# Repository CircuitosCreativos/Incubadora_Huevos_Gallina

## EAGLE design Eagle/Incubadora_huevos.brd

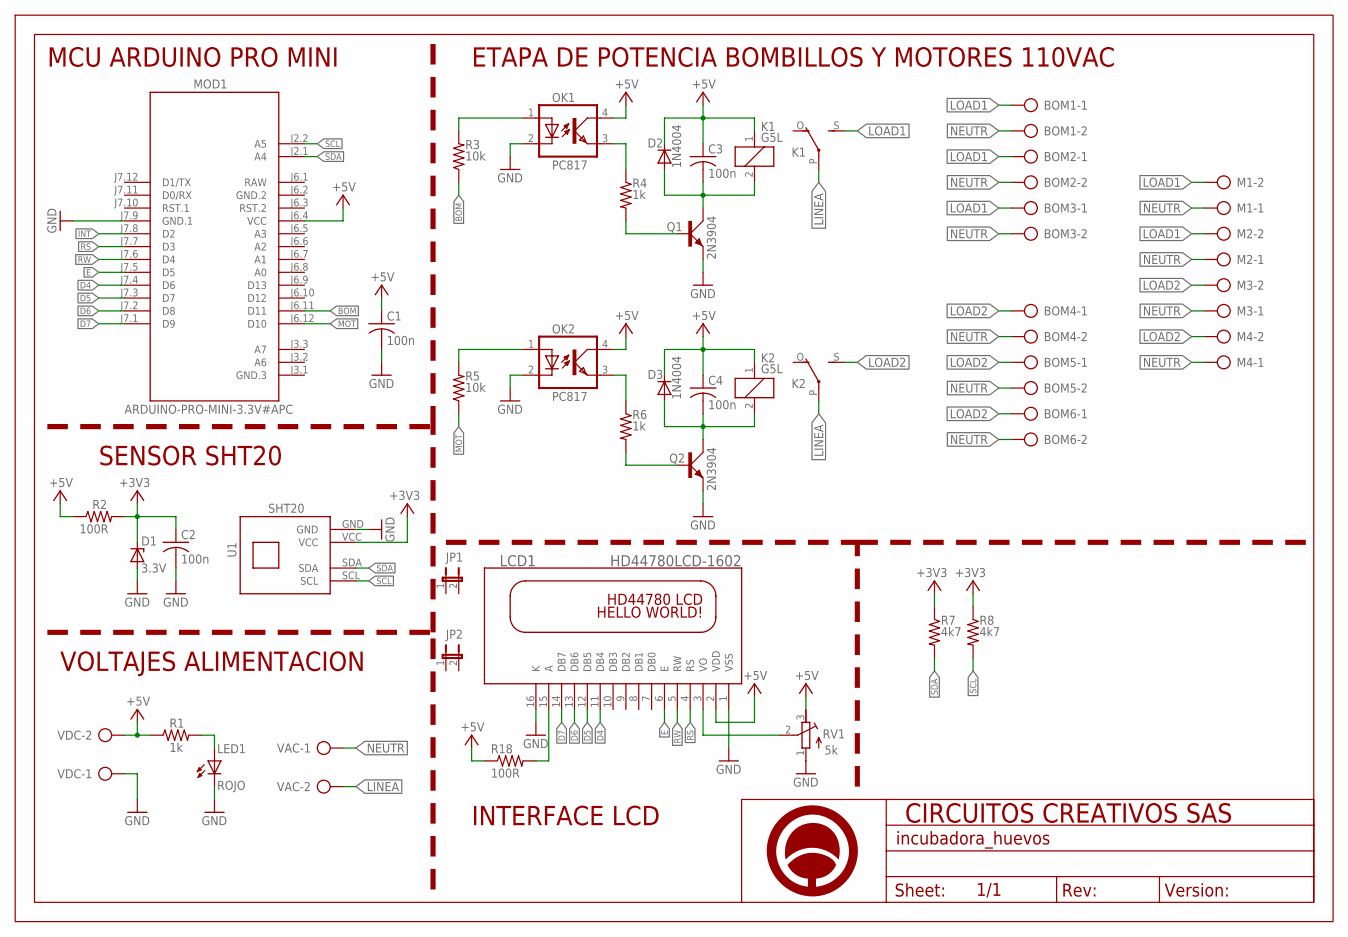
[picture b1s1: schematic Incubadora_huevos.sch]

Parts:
BOM1, BOM2, BOM3, BOM4, BOM5, BOM6: AK500/2
C1, C2, C3, C4: 100n; C025-025X050
D1: 3.3V; DO41Z10
D2, D3: 1N4004; DO41-10
JP1, JP2: JP1E; JP1
K1, K2: G5L; G5LE
LCD1: HD44780LCD-1602; LCD1602
LED1: ROJO; LED3MM
M1, M2, M3, M4: AK500/2
MOD1: ARDUINO-PRO-MINI-3.3V#APC; ARDUINO-PRO-MINI#APC
OK1, OK2: PC817; DIL04
Q1, Q2: 2N3904; TO92D
R1, R4, R6: 1k; 0204/7
R2, R18: 100R; 0204/7
R3, R5: 10k; 0204/7
R7, R8: 4k7; 0204/7
RV1: 5k; RTRIM3296W
U1: SHT20
U$1: A4_HORIZONTAL; LOGO
VAC: AK500/2
VDC: AK500/2

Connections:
+3V3: C2.1, D1.C, R2.2, R7.1, R8.1, U1.VCC
+5V: C1.1, C3.1, C4.1, D2.C, D3.C, K1.1, K2.1, LCD1.2 (VDD), MOD1.J6.4 (VCC), OK1.4 (COL), OK2.4 (COL), R1.1, R2.1, R18.1, RV1.3 (E), VDC.2
BOM: MOD1.J6.11 (D11), R3.1
D4: LCD1.11 (DB4), MOD1.J7.4 (D6)
D5: LCD1.12 (DB5), MOD1.J7.3 (D7)
D6: LCD1.13 (DB6), MOD1.J7.2 (D8)
D7: LCD1.14 (DB7), MOD1.J7.1 (D9)
E: LCD1.6 (E), MOD1.J7.5 (D5)
GND: C1.2, C2.2, D1.A, LCD1.1 (VSS), LCD1.16 (K), LED1.K (C), MOD1.J7.9 (GND.1), OK1.2 (C), OK2.2 (C), Q1.E, Q2.E, RV1.1 (A), U1.GND, VDC.1
GND.2: MOD1.J6.2 (GND.2)
INT: MOD1.J7.8 (D2)
LINEA: K1.P, K2.P, VAC.2
LOAD1: BOM1.1, BOM2.1, BOM3.1, K1.S, M1.2, M2.2
LOAD2: BOM4.1, BOM5.1, BOM6.1, K2.S, M3.2, M4.2
MOT: MOD1.J6.12 (D10), R5.1
unnamed: LED1.A, R1.2
unnamed: OK1.3 (EMIT), R4.1
unnamed: Q1.B, R4.2
unnamed: OK1.1 (A), R3.2
unnamed: C4.2, D3.A, K2.2, Q2.C
unnamed: OK2.3 (EMIT), R6.1
unnamed: Q2.B, R6.2
unnamed: OK2.1 (A), R5.2
unnamed: C3.2, D2.A, K1.2, Q1.C
unnamed: LCD1.3 (VO), RV1.2 (S)
unnamed: LCD1.15 (A), R18.2
NEUTR: BOM1.2, BOM2.2, BOM3.2, BOM4.2, BOM5.2, BOM6.2, M1.1, M2.1, M3.1, M4.1, VAC.1
RAW: MOD1.J6.1 (RAW)
RS: LCD1.4 (RS), MOD1.J7.7 (D3)
RW: LCD1.5 (RW), MOD1.J7.6 (D4)
SCL: MOD1.J2.2 (A5), R8.2, U1.SCL
SDA: MOD1.J2.1 (A4), R7.2, U1.SDA

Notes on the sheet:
SENSOR SHT20
MCU ARDUINO PRO MINI
VOLTAJES ALIMENTACION
ETAPA DE POTENCIA BOMBILLOS Y MOTORES 110VAC
INTERFACE LCD

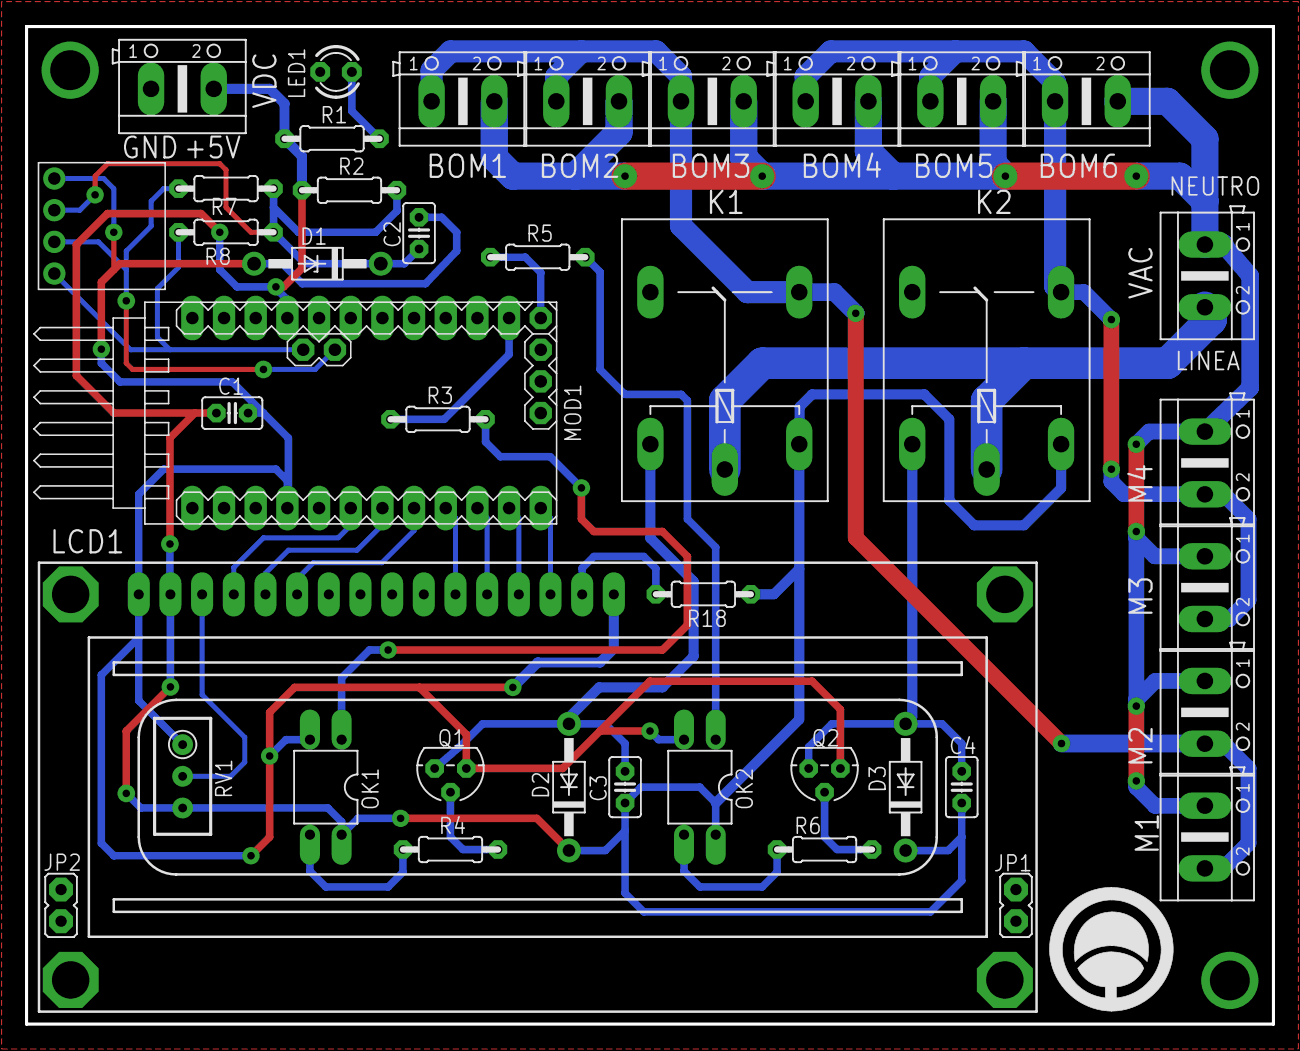
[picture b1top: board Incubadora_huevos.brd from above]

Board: 2 copper layers, 100.0 x 80.0 mm, 42 parts (0 on the bottom side), 29 nets.

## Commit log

2018-09-25 Terminado SCH circuito basico ON-OFF
2018-09-25 Inicio BRD, ubicando componentes
2018-09-26 Terminado ubicacion componentes. inicio ruteo
2018-12-12 Terminado BRD, listo para fabricar
2018-12-12 Se modifico la etapa de potencia ya que la anterior se calentaba mucho
2019-01-26 Subido Firmware para el microcontrolador
2019-01-26 Subido archivos restantes version 1.0
2019-01-26 Cambio sensor SHT20 por DS18B20, por problemas de distancia en I2C
2019-01-26 Se agrego resistencias pull up a la PCB
2019-01-26 Se agrego rutina falla de conexion sensor

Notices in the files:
parts and their libraries:
DIY- comercial modules: Released under the Creative Commons Attribution 4.0 International License: http://creativecommons.org/licenses/by/4.0
